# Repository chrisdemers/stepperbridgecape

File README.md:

This is a Beaglebone Stepper Motor Bridge Cape

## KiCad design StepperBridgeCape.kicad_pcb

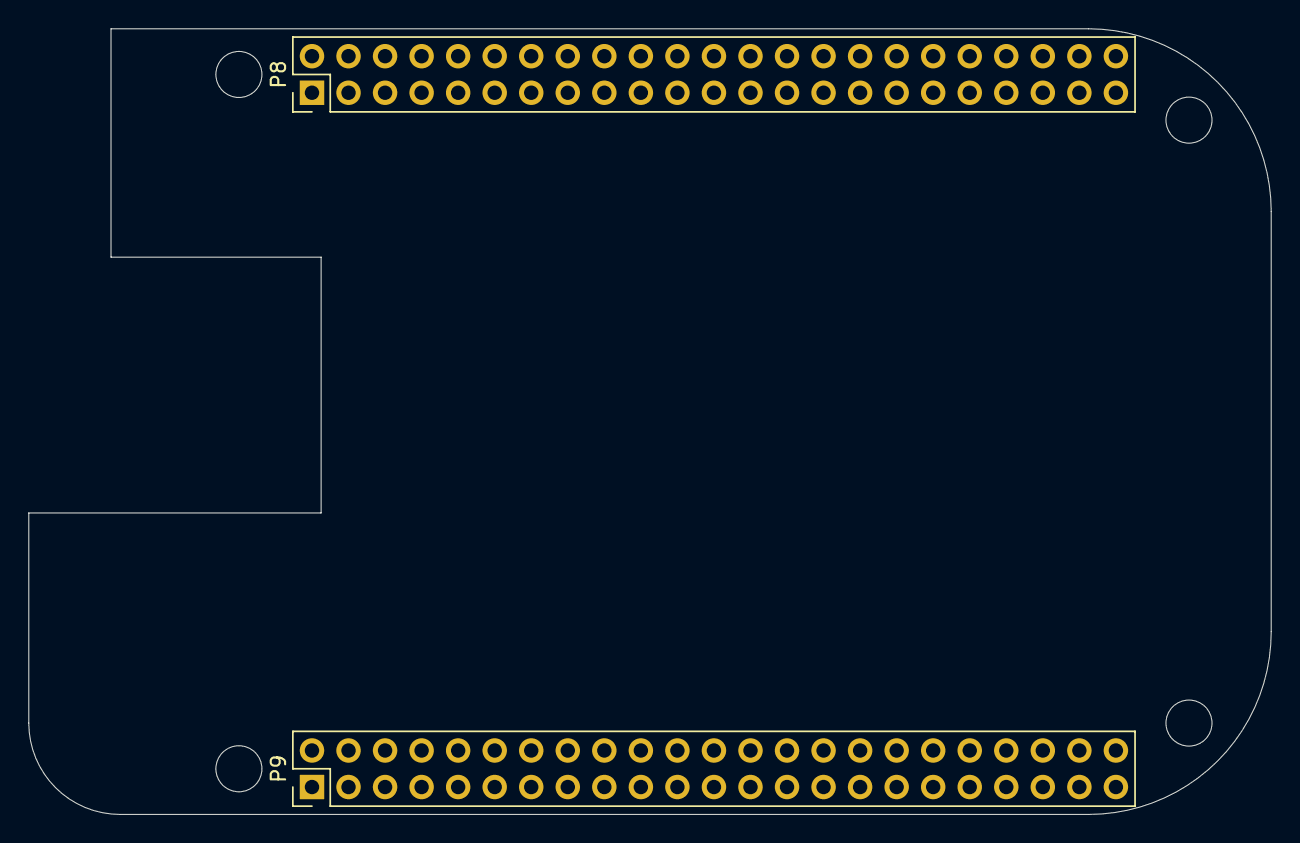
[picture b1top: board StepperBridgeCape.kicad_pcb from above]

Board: 2 copper layers, 86.4 x 54.6 mm, 6 parts (0 on the bottom side), 4 nets, no tracks yet.

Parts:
MH1, MH2, MH3, MH4: MountingHole_3.2mm_M3_DIN965
P8, P9: BeagleBone_Black_Header; PinHeader_2x23_P2.54mm_Vertical

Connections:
+3V3: P9.3, P9.4
+5V: P9.5, P9.6
GNDD: P8.1, P8.2, P9.1, P9.2, P9.43, P9.44, P9.45, P9.46
VBUS: P9.7, P9.8

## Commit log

2025-12-17 Initial Revision
2025-12-17 Remove original files
